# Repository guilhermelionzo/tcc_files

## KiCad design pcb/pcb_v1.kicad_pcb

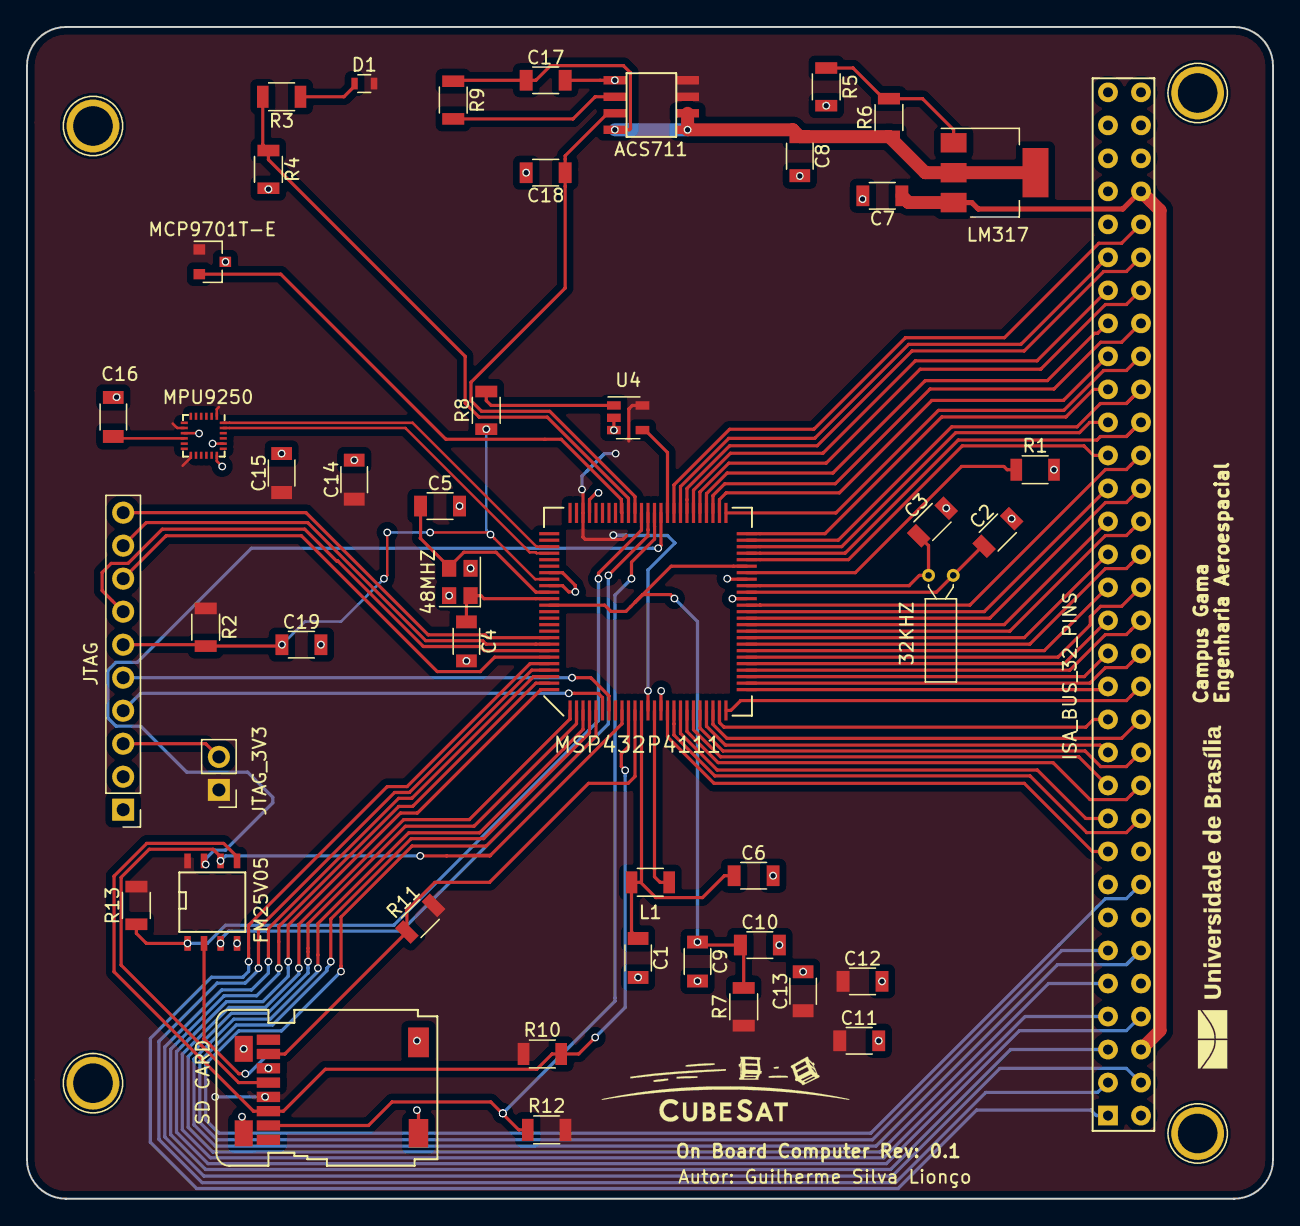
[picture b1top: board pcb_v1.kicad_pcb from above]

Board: 2 copper layers, 95.9 x 90.2 mm, 47 parts (0 on the bottom side), 86 nets.

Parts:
32KHZ: 32kHz; Crystal_DS26_d2.0mm_l6.0mm_Horizontal
48MHZ: 48MHz; Oscillator_SMD_Abracon_ASE-4pin_3.2x2.5mm
ACS711: ACS711; ACS711_8-pin SOICN
C1, C7, C8, C9, C10, C11, C12: 0,1uF; C_1206
C2, C3, C4, C5: 22p; C_1206
C6: 4u7; C_1206
C13: 10u; C_1206
C14: 10nF; C_1206
C15, C16, C17: 0.1uF; C_1206
C18: 0.56nF; C_1206
C19: 1nF; C_1206
D1: LED; R_0603
FM25V05: FM25V05; SOIC-8-N
ISA_BUS_32_PINS: ISA_BUS_connector; ISA_CONNECTOR
JTAG: CONN_01X10; Pin_Header_Straight_1x10_Pitch2.54mm
JTAG_3V3: CONN_01X02; Pin_Header_Straight_1x02_Pitch2.54mm
L1: 4.7uH; L_1206
LM317: LM317_SOT223; SOT-223-3_TabPin2
MCP9701T-E: MCP9701T-E/TTCT-ND; SOT-23
MPU9250: MPU-9250; QFN-24_3x3mm_Pitch0.4mm
MSP432P4111: MSP432P4111
R1: 91kOhm; R_1206
R2: 47K; R_1206
R3: 49K9; R_1206
R4: 68K1; R_1206
R5: 240; R_1206
R6: 140; R_1206
R7: 0R; R_1206
R8: 4.7K; R_1206
R9: 1K; R_1206
R10, R11, R12, R13: 49k9; R_1206
SD CARD: ST1W008S4ER; ST1W008S4ER1500
U4: STWD100; SOT-23-5

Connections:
+5V: C7.1, ISA_BUS_32_PINS.35, ISA_BUS_32_PINS.61, LM317.3
/3v3: ACS711.1, ACS711.2, ACS711.8, C8.1, C17.1, LM317.2, R6.1, R9.1
/3v3_ACS: ACS711.3, ACS711.4, C11.1, C12.1, C13.1, C14.1, C15.1, D1.2, FM25V05.8, JTAG_3V3.1, MCP9701T-E.1, MPU9250.1, MPU9250.8, MPU9250.13, MSP432P4111.13, MSP432P4111.73, R2.1, R7.1, R10.1, R11.2, R12.2, R13.2, SD CARD.4, U4.5
/HFXIN: 48MHZ.1, C4.1, MSP432P4111.86
/HFXOUT: 48MHZ.3, C5.1, MSP432P4111.85
/LFXIN: 32KHZ.2, C2.1, MSP432P4111.41
/LFXOUT: 32KHZ.1, C3.1, MSP432P4111.42
/VCORE: C1.1, C6.1, L1.2, MSP432P4111.12
/VSW: L1.1, MSP432P4111.14
/adcVoltage3V3: MSP432P4111.66, R3.2, R4.1
/analog_vcc: C9.1, C10.1, MSP432P4111.45, MSP432P4111.87, R7.2
/chipSelectorFRAM: FM25V05.1, MSP432P4111.64, R13.1
/chipSelectorSD: MSP432P4111.62, R12.1, SD CARD.2
/clkIMU: MPU9250.23, MSP432P4111.79
/clkMemory: FM25V05.6, MSP432P4111.9, SD CARD.5
/currentSensor: ACS711.7, C18.1, MSP432P4111.65
/holdFRAM: FM25V05.7, MSP432P4111.61
/jtag/JTAG_3v3: JTAG.3, JTAG_3V3.2
/jtag_bclUartRxd: JTAG.4, MSP432P4111.6
/jtag_bclUartTxd: JTAG.5, MSP432P4111.7
/jtag_tckSwdClk: JTAG.8, MSP432P4111.95
/jtag_tdi: JTAG.10, MSP432P4111.92
/jtag_tdoSwo: JTAG.9, MSP432P4111.93
/jtag_tmsSwdio: JTAG.7, MSP432P4111.94
/misoMemory: FM25V05.2, MSP432P4111.11, R11.1, SD CARD.7
/mosiMemory: FM25V05.5, MSP432P4111.10, R10.2, SD CARD.3
/p1: ISA_BUS_32_PINS.4, MSP432P4111.1
/p2: ISA_BUS_32_PINS.5, MSP432P4111.2
/p3: ISA_BUS_32_PINS.38, MSP432P4111.3
/p4: ISA_BUS_32_PINS.6, MSP432P4111.4
/p5: ISA_BUS_32_PINS.40, MSP432P4111.5
/p16: ISA_BUS_32_PINS.9, MSP432P4111.16
/p17: ISA_BUS_32_PINS.42, MSP432P4111.17
/p18: ISA_BUS_32_PINS.10, MSP432P4111.18
/p19: ISA_BUS_32_PINS.43, MSP432P4111.19
/p20: ISA_BUS_32_PINS.11, MSP432P4111.20
/p21: ISA_BUS_32_PINS.44, MSP432P4111.21
/p22: ISA_BUS_32_PINS.12, MSP432P4111.22
/p23: ISA_BUS_32_PINS.45, MSP432P4111.23
/p24: ISA_BUS_32_PINS.13, MSP432P4111.24
/p25: ISA_BUS_32_PINS.46, MSP432P4111.25
/p26: ISA_BUS_32_PINS.14, MSP432P4111.26
/p27: ISA_BUS_32_PINS.47, MSP432P4111.27
/p28: ISA_BUS_32_PINS.15, MSP432P4111.28
/p29: ISA_BUS_32_PINS.48, MSP432P4111.29
/p30: ISA_BUS_32_PINS.16, MSP432P4111.30
/p31: ISA_BUS_32_PINS.49, MSP432P4111.31
/p32: ISA_BUS_32_PINS.17, MSP432P4111.32
/p33: ISA_BUS_32_PINS.50, MSP432P4111.33
/p34: ISA_BUS_32_PINS.18, MSP432P4111.34
/p35: ISA_BUS_32_PINS.51, MSP432P4111.35
/p36: ISA_BUS_32_PINS.19, MSP432P4111.36
/p37: ISA_BUS_32_PINS.52, MSP432P4111.37
/p38: ISA_BUS_32_PINS.20, MSP432P4111.38
/p39: ISA_BUS_32_PINS.53, MSP432P4111.39
/p46: ISA_BUS_32_PINS.21, MSP432P4111.46
/p47: ISA_BUS_32_PINS.54, MSP432P4111.47
/p48: ISA_BUS_32_PINS.22, MSP432P4111.48
/p49: ISA_BUS_32_PINS.55, MSP432P4111.49
/p50: ISA_BUS_32_PINS.23, MSP432P4111.50
/p51: ISA_BUS_32_PINS.56, MSP432P4111.51
/p52: ISA_BUS_32_PINS.24, MSP432P4111.52
/p53: ISA_BUS_32_PINS.57, MSP432P4111.53
/p54: ISA_BUS_32_PINS.25, MSP432P4111.54
/p55: ISA_BUS_32_PINS.58, MSP432P4111.55
/p56: ISA_BUS_32_PINS.26, MSP432P4111.56
/p57: ISA_BUS_32_PINS.59, MSP432P4111.57
/p58: ISA_BUS_32_PINS.27, MSP432P4111.58
/p59: ISA_BUS_32_PINS.60, MSP432P4111.59
/p96: ISA_BUS_32_PINS.1, MSP432P4111.96
/p97: ISA_BUS_32_PINS.2, MSP432P4111.97
/p98: ISA_BUS_32_PINS.34, MSP432P4111.98
/p99: ISA_BUS_32_PINS.3, MSP432P4111.99
/p100: ISA_BUS_32_PINS.36, MSP432P4111.100
/resetMCU: C19.1, JTAG.6, MSP432P4111.83, R2.2, R8.1
/sdaIMU: MPU9250.24, MSP432P4111.78
/temperatureSensor: MCP9701T-E.2, MSP432P4111.67
/wpFRAM: FM25V05.3, MSP432P4111.63
/wtdToggle: MSP432P4111.60, U4.4
GND: 48MHZ.2, 48MHZ.4, ACS711.5, C1.2, C2.2, C3.2, C4.2, C5.2, C6.2, C7.2, C8.2, C9.2, C10.2, C11.2, C12.2, C13.2, C14.2, C15.2, C16.2, C17.2, C18.2, C19.2, FM25V05.4, ISA_BUS_32_PINS.32, ISA_BUS_32_PINS.33, ISA_BUS_32_PINS.63, ISA_BUS_32_PINS.64, JTAG.1, MCP9701T-E.3, MPU9250.9, MPU9250.18, MPU9250.20, MSP432P4111.15, MSP432P4111.40, MSP432P4111.43, MSP432P4111.72, MSP432P4111.82, MSP432P4111.84, R1.2, R4.2, R5.2, SD CARD.6, SD CARD.9, SD CARD.10, SD CARD.12, U4.2, U4.3
unnamed: C16.1, MPU9250.10
unnamed: D1.1, R3.1
unnamed: MSP432P4111.44, R1.1
unnamed: LM317.1, R5.1, R6.2
unnamed: R8.2, U4.1
unnamed: ACS711.6, R9.2

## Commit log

2019-06-17 1° commit
2019-06-17 Clean up Kicad and TCC
    Some changes in the
2019-06-17 Kicad and TCC clean up :muscle:
2019-06-18 clean up e Periphecic update
2019-06-18 add logo in the PCB
2019-06-19 add flowcharts
2019-06-20 update CSS
    Operations Mode + UML +State Machine
2019-06-25 modify Image's caption position
2019-06-26 code clean up :droplet:
2019-06-26 update "modos de operação" + traces
2019-06-26 add all operation modes and the descriptions in each state
2019-06-28 add conclusion/recomendations + code clean up
2019-07-05 add feedback Aguayo | ongoing
2019-07-10 update wdt and launchpad section
2019-07-23 TTC clean up
2019-09-15 tcc Final
2019-12-02 update images
2019-12-02 add architecture image
